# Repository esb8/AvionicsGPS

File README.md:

## Overview

This project is a RP2040, GPS board designed to be utilized in an avionics system comprising of 3 CAN connected PCBs which are comprised of a sensorboard, a powerboard, and a GPS Board. 
This avionics stack is designed for use in High Power model rocketry and aims to provide accurate telemetry, tracking position, altitude, and time during flight.

## 📡 PCB Features

- L86-M33 -165 dBm GPS
- Integrated Patch Antenna
- CAN Transiecver
- RP2040
- USB-C Connection
- 5V -> 3.3V regulated power input
- Onboard status LEDs for VBUS, MCU and GPS debugging
- External 128Mbit Flash Memory

## 📷 Media 
**Schematic**

**PCB**

**3D Model**

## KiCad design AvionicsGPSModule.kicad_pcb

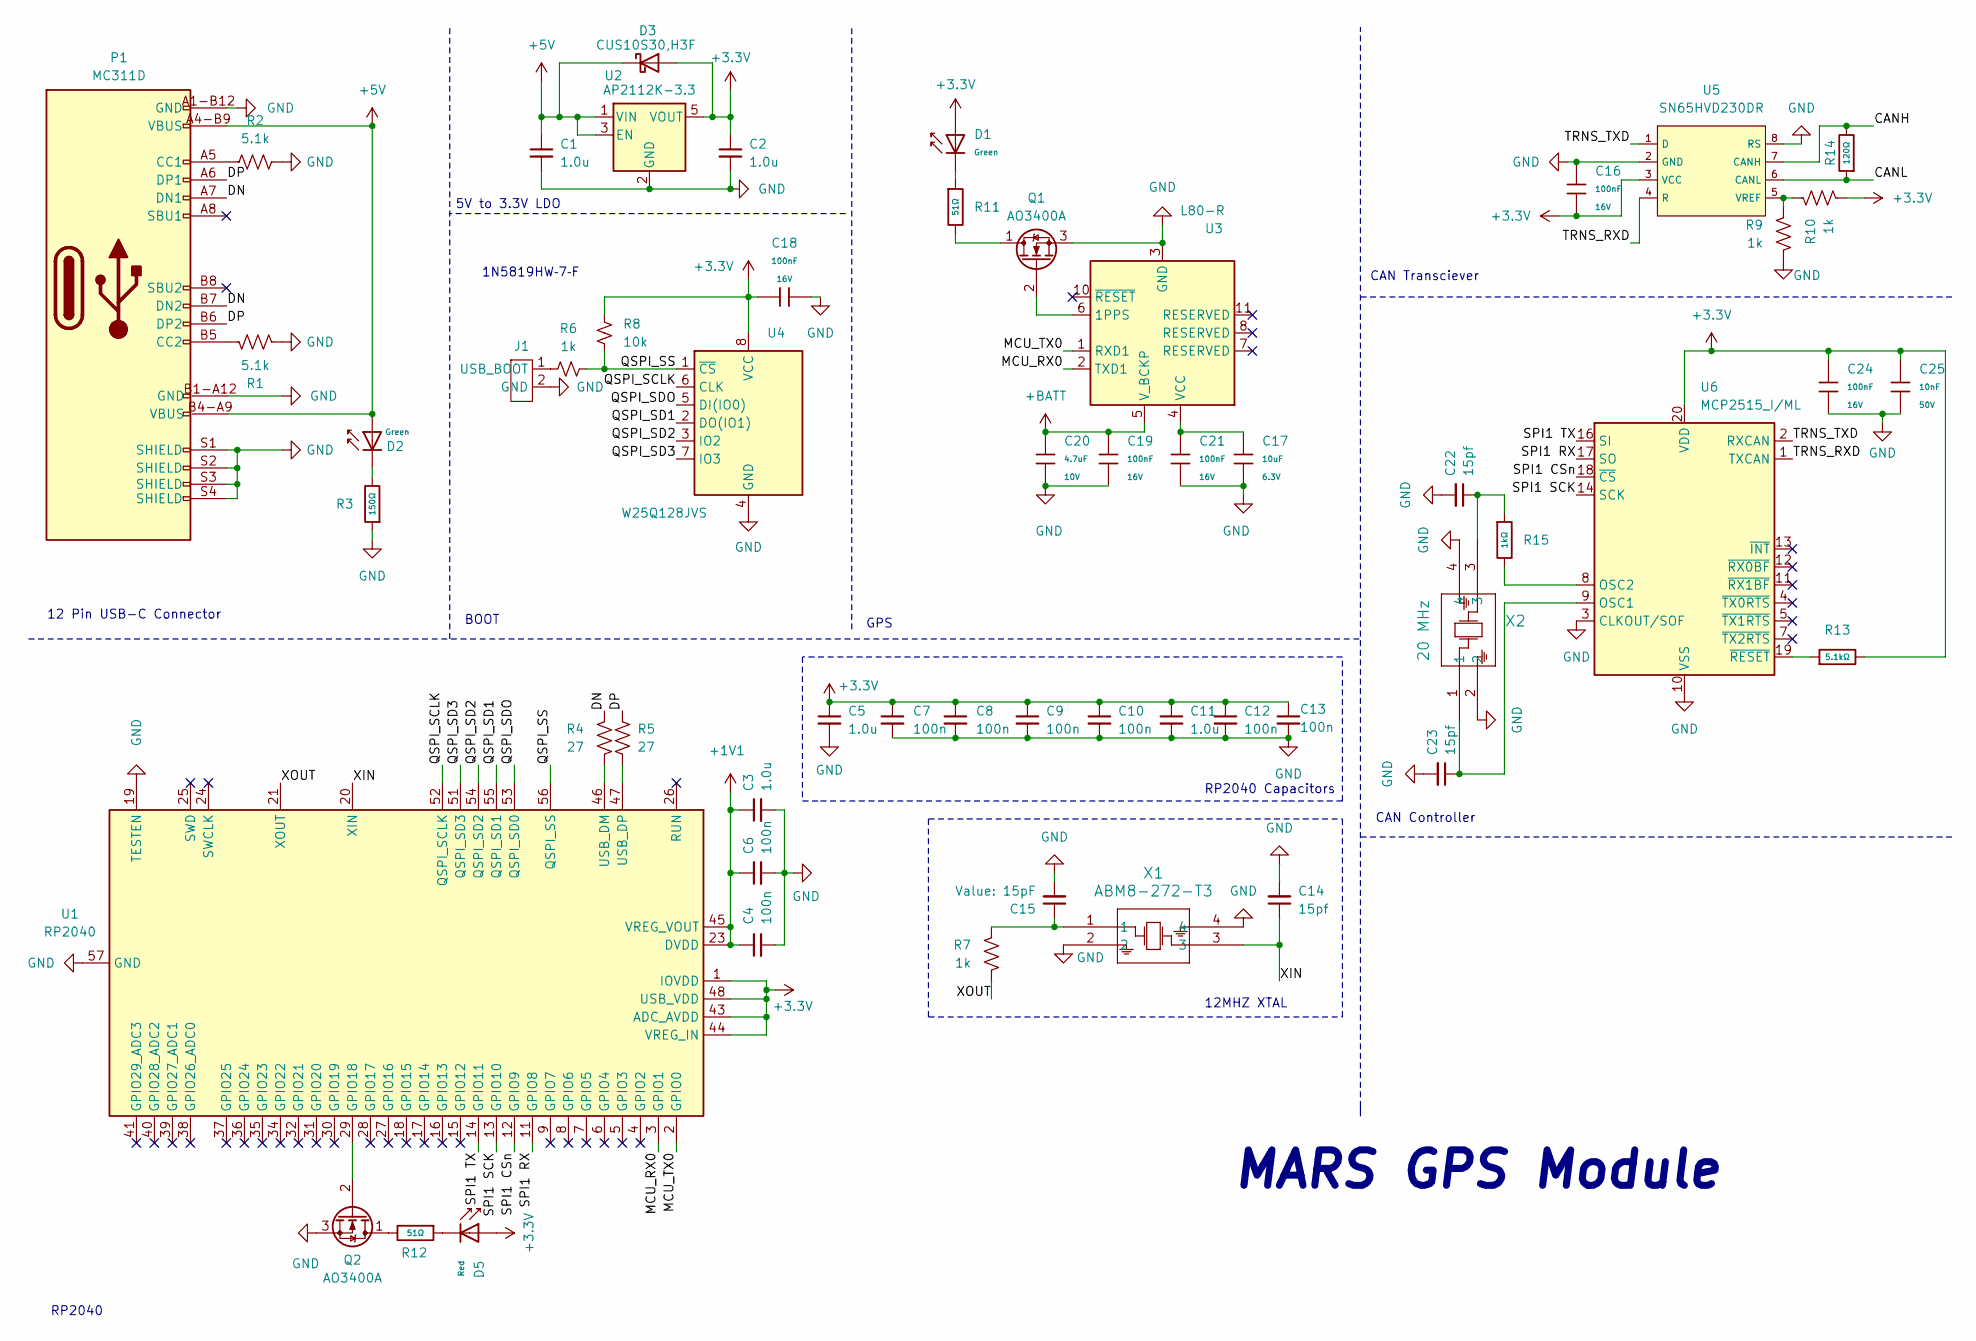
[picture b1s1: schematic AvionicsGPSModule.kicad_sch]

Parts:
C1, C2, C3, C5: 1.0u; C_0402_1005Metric; LCSC C14445
C4, C6, C7, C8, C9, C10, C12, C13: 100n; C_0402_1005Metric; LCSC C1525
C11: 1.0u; C_0402_1005Metric; LCSC C1525
C14, C22, C23: 15pf; C_0402_1005Metric; LCSC C1548
C15: 15pF; C_0402_1005Metric; LCSC C1548
C16, C24: 100nF; C_0402; Voltage Rated 16V; Tolerance ±10%; Part CL05B104KO5NNNC; LCSC C1525
C17: 10uF; C_0402_1005Metric; Voltage Rated 6.3V; Tolerance ±20%; Part CL05A106MQ5NUNC; LCSC C15525
C18, C19, C21: 100nF; C_0402_1005Metric; Voltage Rated 16V; Tolerance ±10%; Part CL05B104KO5NNNC; LCSC C1525
C20: 4.7uF; C_0402_1005Metric; Voltage Rated 10V; Tolerance ±20%; Part CL05A475MP5NRNC; LCSC C23733
C25: 10nF; C_0402; Voltage Rated 50V; Tolerance ±10%; Part CL05B103KB5NNNC; LCSC C15195
D1, D2: Green; D_0805; Part KT-0805G; LCSC C2297
D3: CUS10S30,H3F; D_SOD-323; LCSC C146335
D5: Red; D_0805; Forward Voltage (VF) 1.6V~2.6V; Part NCD0805R1; LCSC C84256
J1: PinHeader_1x02_P2.54mm_Vertical
P1: MC311D; USB_C_Receptacle_GCT_USB4105-xx-A_16P_TopMnt_Horizontal; LCSC C136423
Q1, Q2: AO3400A; SOT-23-3L_AOS; LCSC C20917
R1, R2: 5.1k; R_0402_1005Metric; LCSC C25905
R3: 150Ω; R_0402; Overload Voltage (Max) 50V; Tolerance ±1%; Part 0402WGF1500TCE; LCSC C25082
R4, R5: 27; R_0402_1005Metric; LCSC C25100
R6, R7, R9, R10: 1k; R_0402_1005Metric; LCSC C11702
R8: 10k; R_0402_1005Metric; LCSC C25531
R11, R12: 51Ω; R_0402; Overload Voltage (Max) 50V; Tolerance ±1%; Part 0402WGF510JTCE; LCSC C25125
R13: 5.1kΩ; R_0402; Overload Voltage (Max) 50V; Tolerance ±1%; Part 0402WGF5101TCE; LCSC C25905
R14: 120Ω; R_0402; Overload Voltage (Max) 50V; Tolerance ±1%; Part 0402WGF1200TCE; LCSC C25079
R15: 1kΩ; R_0402; Overload Voltage (Max) 50V; Tolerance ±1%; Part 0402WGF1001TCE; LCSC C11702
U1: RP2040; QFN-56-1EP_7x7mm_P0.4mm_EP3.2x3.2mm; LCSC C2040
U2: AP2112K-3.3; SOT-23-5; LCSC C51118
U3: L80-R; Quectel_L80-R; LCSC C188357
U4: W25Q128JVS; SOIC-8_5.3x5.3mm_P1.27mm; LCSC C97521
U5: SN65HVD230DR; SOIC-8_L4.9-W3.9-P1.27-LS6.0-BL; Supply Voltage 3V~3.6V; Part SN65HVD230DR; LCSC C12084
U6: MCP2515_I/ML; QFN-20-1EP_4x4mm_P0.5mm_EP2.5x2.5mm; LCSC C96140
X1: ABM8-272-T3; ABM8-272-T3_ABR; LCSC C20625731
X2: 20 MHz; Crystal_SMD_2016-4Pin_2.0x1.6mm; LCSC C255878

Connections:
+1V1: C3.1, C4.1, C6.1, U1.23 (DVDD), U1.45 (VREG_VOUT), U1.50 (DVDD); also elsewhere on the board
+3.3V: C2.1, C5.1, C7.1, C8.1, C9.1, C10.1, C11.1, C12.1, C13.1, C16.2, C18.1, C24.1, C25.1, D1.2, D3.2 (A), D5.2, R8.1, R10.2, R13.2, U1.1 (IOVDD), U1.10 (IOVDD), U1.22 (IOVDD), U1.33 (IOVDD), U1.42 (IOVDD), U1.43 (ADC_AVDD), U1.44 (VREG_IN), U1.48 (USB_VDD), U1.49 (IOVDD), U2.5 (VOUT), U4.8 (VCC), U5.3 (VCC), U6.20 (VDD)
+5V: C1.1, D2.2, D3.1 (K), P1.A4-B9 (VBUS), P1.B4-A9 (VBUS), U2.1 (VIN), U2.3 (EN)
+BATT: C19.1, C20.1, U3.5 (V_BCKP)
/CANH: R14.2, U5.7 (CANH)
/CANL: R14.1, U5.6 (CANL)
/DN: P1.A7 (DN1), P1.B7 (DN2), R4.1
/DP: P1.A6 (DP1), P1.B6 (DP2), R5.1
/MCU_RX0: U1.3 (GPIO1), U3.2 (TXD1)
/MCU_TX0: U1.2 (GPIO0), U3.1 (RXD1)
/QSPI_SCLK: U1.52 (QSPI_SCLK), U4.6 (CLK)
/QSPI_SD1: U1.55 (QSPI_SD1), U4.2 (DO(IO1))
/QSPI_SD2: U1.54 (QSPI_SD2), U4.3 (IO2)
/QSPI_SD3: U1.51 (QSPI_SD3), U4.7 (IO3)
/QSPI_SDO: U1.53 (QSPI_SD0), U4.5 (DI(IO0))
/QSPI_SS: R6.2, R8.2, U1.56 (QSPI_SS), U4.1 (~CS)
/SPI1 CSn: U1.12 (GPIO9), U6.18 (~CS)
/SPI1 RX: U1.11 (GPIO8), U6.17 (SO)
/SPI1 SCK: U1.13 (GPIO10), U6.14 (SCK)
/SPI1 TX: U1.14 (GPIO11), U6.16 (SI)
/TRNS_RXD: U5.4 (R), U6.1 (TXCAN)
/TRNS_TXD: U5.1 (D), U6.2 (RXCAN)
/XIN: C14.1, U1.20 (XIN), X1.3
/XOUT: R7.2, U1.21 (XOUT)
GND: C1.2, C2.2, C3.2, C4.2, C5.2, C6.2, C7.2, C8.2, C9.2, C10.2, C11.2, C12.2, C13.2, C14.2, C15.2, C16.1, C17.2, C18.2, C19.2, C20.2, C21.2, C22.2, C23.2, C24.2, C25.2, J1.2 (GND), P1.A1-B12 (GND), P1.B1-A12 (GND), P1.S1 (SHIELD), P1.S2 (SHIELD), P1.S3 (SHIELD), P1.S4 (SHIELD), Q1.3 (S), Q2.3 (S), R1.2, R2.2, R3.1, R9.2, U1.19 (TESTEN), U1.57 (GND), U2.2 (GND), U3.3 (GND), U3.12 (GND), U4.4 (GND), U5.2 (GND), U5.8 (RS), U6.3 (CLKOUT/SOF), U6.10 (VSS), X1.2, X1.4, X2.2, X2.4; also elsewhere on the board
unnamed: C15.1, R7.1, X1.1
unnamed: C22.1, R15.1, X2.3
unnamed: D1.1, R11.1
unnamed: D2.1, R3.2
unnamed: D5.1, R12.1
unnamed: J1.1 (USB_BOOT), R6.1
unnamed: P1.A5 (CC1), R2.1
unnamed: P1.B5 (CC2), R1.1
unnamed: Q1.1 (D), R11.2
unnamed: Q1.2 (G), U3.6 (1PPS)
unnamed: Q2.1 (D), R12.2
unnamed: Q2.2 (G), U1.29 (GPIO18)
unnamed: R4.2, U1.46 (USB_DM)
unnamed: R5.2, U1.47 (USB_DP)
unnamed: C17.1, C21.1, U3.4 (VCC)
unnamed: R9.1, R10.1, U5.5 (VREF)
unnamed: C23.1, U6.9 (OSC1), X2.1
unnamed: R15.2, U6.8 (OSC2)
unnamed: R13.1, U6.19 (~RESET)

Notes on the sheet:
12 Pin USB-C Connector
1N5819HW‑7‑F
MARS GPS Module
CAN Transciever
CAN Controller
RP2040 Capacitors
5V to 3.3V LDO
12MHZ XTAL
RP2040
BOOT
GPS

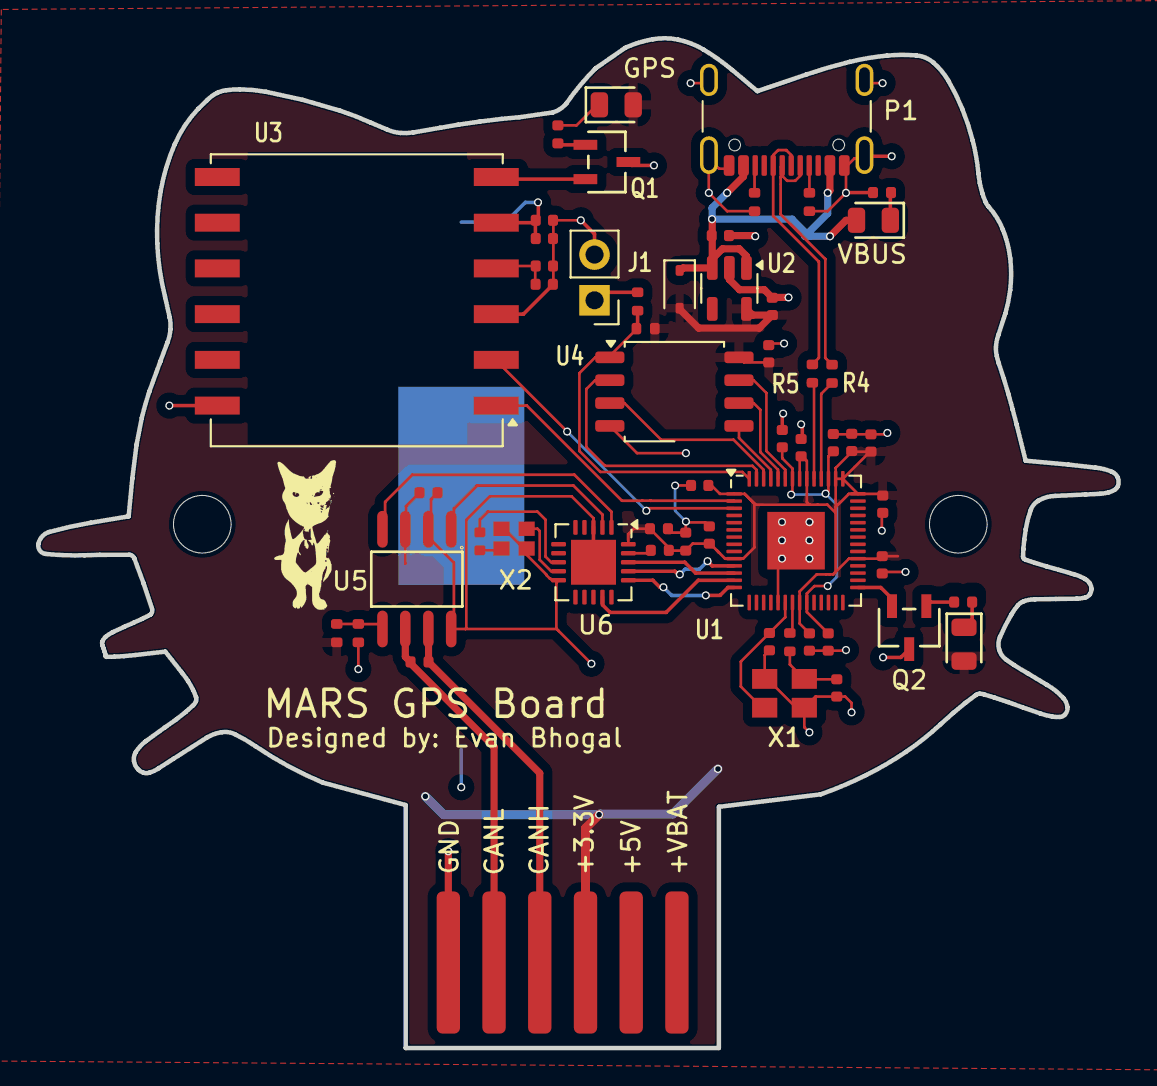
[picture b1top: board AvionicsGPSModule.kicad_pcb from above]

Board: 4 copper layers, 60.0 x 56.1 mm, 54 parts (0 on the bottom side), 44 nets.

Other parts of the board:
C6#2: 100n; C_0402_1005Metric

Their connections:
+1V1: C6#2.1; also elsewhere on the board
GND: C6#2.2; also elsewhere on the board

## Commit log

2025-03-30 Imported Project
2025-03-31 PCB Created
2025-03-31 Connector Changes
2025-04-06 Fix: Moved RP2040 capacitors
    Fix: Corrected Design Rules for clearance and width
    Fix: Correctly Annotated capacitors
2025-04-07 finalized wiring
2025-04-29 Fixed connector placement and GND vias
2025-04-29 Added JLC DRC requirements, and managed libraries for simpler forking
2025-05-05 Fixed Differential Pair Wiring
2025-05-26 minor changes
2025-06-11 Added mounting holes and LEDs, changed outline
2025-06-13 Added Marketing, fulfilled DRC, finalized board
2025-06-30 added CAN Transciever
2025-07-03 Added CAN Transciever and CAN Controller
2025-07-03 Updated BOM, made schematic cleaner
2025-07-04 Respecced crystal, added Schottky Diode
2025-07-04 Fixed Mounting Pad for CAN Controller
2025-07-04 Fixed MOSFET Driver
